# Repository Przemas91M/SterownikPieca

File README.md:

# Sterownik pompy pieca CO
Prosty sterownik pompy obiegowej pieca CO w oparciu o mikrokontroler ATmega328P-AU.  
Sterownik składa się z:
- czujnika temperatury DS18B20,
- wyświetlacza LCD 2x18,
- enkodera obrotowego dla zadawania nastaw temperatury,
- 2x przekaźniki do załączania pompy i buzzera ostrzegawczego.    
Sterownik załącza pompę, gdy temperatura wody w piecu osiągnie 30 st C.  
Powyżej 70 st C załącza się buzzer ostrzegawczy, aby nie zagotować wody w obiegu grzewczym.  
Gdy temperatura spadnie poniżej 30 st C, pompa jest wyłączana.

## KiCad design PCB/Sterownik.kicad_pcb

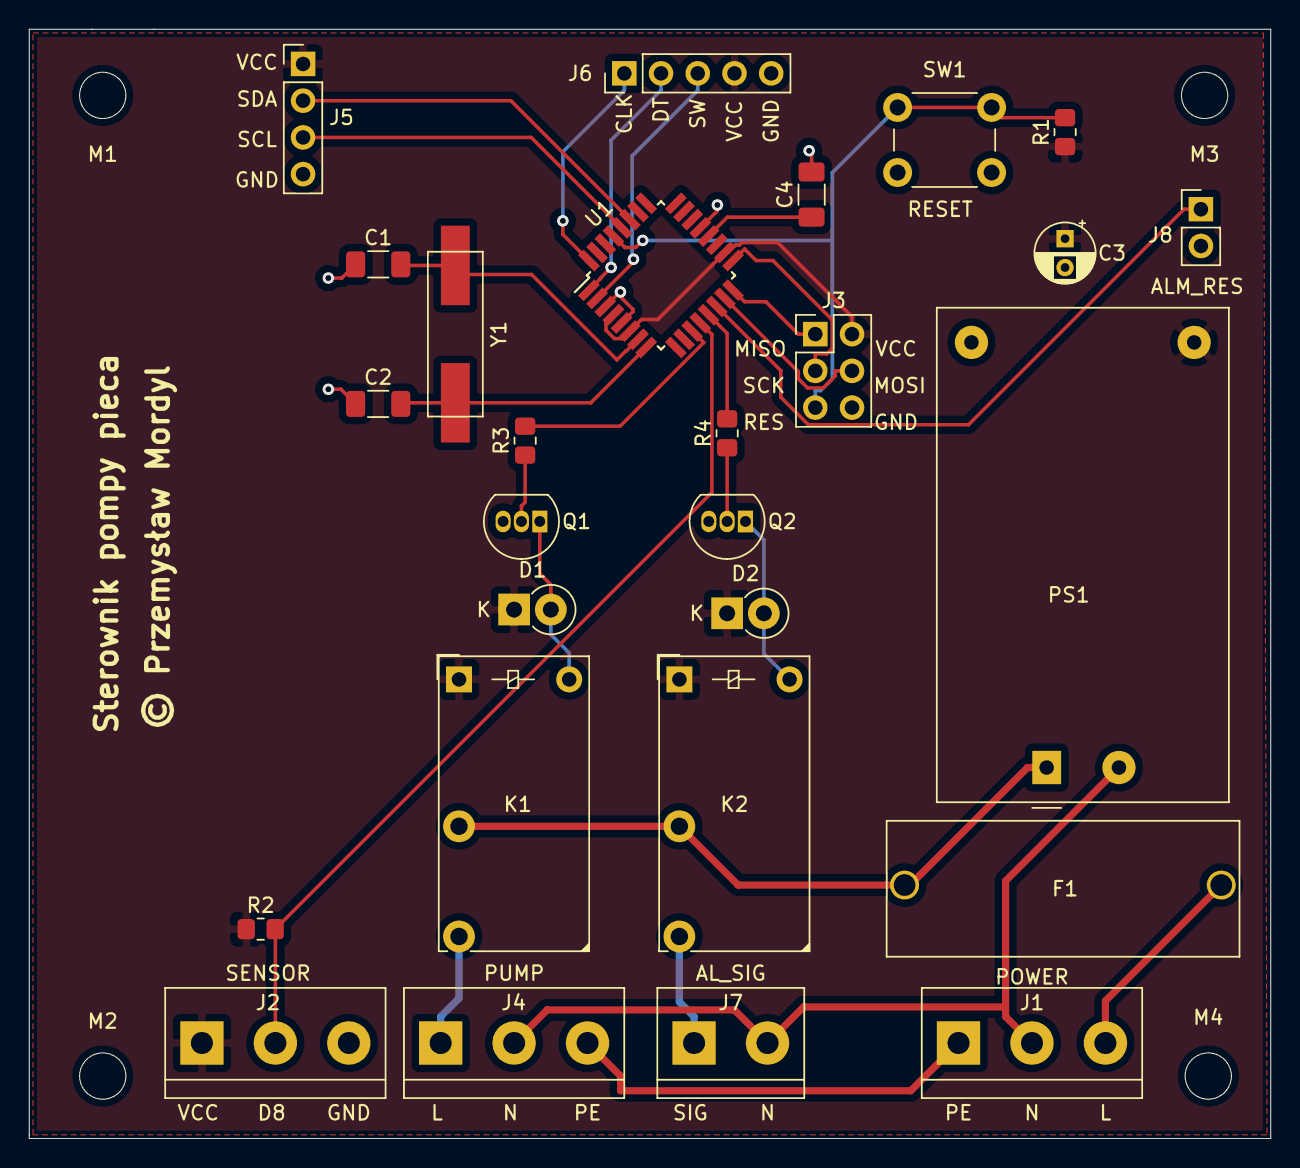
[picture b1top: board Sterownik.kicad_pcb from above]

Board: 2 copper layers, 85.9 x 76.7 mm, 31 parts (0 on the bottom side), 28 nets.

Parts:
C1, C2: C; C_1206_3216Metric_Pad1.33x1.80mm_HandSolder
C3: 220uF; CP_Radial_D4.0mm_P2.00mm
C4: 100nF; C_1206_3216Metric_Pad1.33x1.80mm_HandSolder
D1, D2: 1N4007; D_DO-41_SOD81_P2.54mm_Vertical_KathodeUp
F1: 1A; FuseHolder PTF-78
J1: Zasilanie 230VAC; TerminalBlock_bornier-3_P5.08mm
J2: Złącze DS18B20; TerminalBlock_bornier-3_P5.08mm
J3: Conn_02x03_Odd_Even; PinHeader_2x03_P2.54mm_Vertical
J4: Złącze pompy; TerminalBlock_bornier-3_P5.08mm
J5: Wyświetlacz LCD; PinHeader_1x04_P2.54mm_Vertical
J6: Enkoder obrotowy; PinHeader_1x05_P2.54mm_Vertical
J7: Złącze brzęczyka; TerminalBlock_bornier-2_P5.08mm
J8: Złącze kasowania alarmu; PinHeader_1x02_P2.54mm_Vertical
K1: Załączenie pompy; Relay_SPST_Finder_32.21-x300
K2: Załączenie sygnalizatora alarmu; Relay_SPST_Finder_32.21-x300
M1, M2, M3, M4: MountingHole_3.2mm_M3_DIN965
PS1: HLK-PM01; Converter_ACDC_HiLink_HLK-PMxx
Q1, Q2: BC182; TO-92_Inline
R1: 10K; R_0805_2012Metric_Pad1.20x1.40mm_HandSolder
R2, R3, R4: 4,7K; R_0805_2012Metric_Pad1.20x1.40mm_HandSolder
SW1: SW_Push; SW_PUSH_6mm
U1: ATmega328P-AU; TQFP-32_7x7mm_P0.8mm
Y1: Crystal; Crystal_16MHz_SMD

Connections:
/L: F1.2, J1.3
/N: J1.2, J4.2, J7.2, PS1.2
/PE: J1.1, J4.3
A4: J5.2, U1.27
A5: J5.3, U1.28
D2: J6.1, U1.32
D3: J6.2, U1.1
D4: J6.3, U1.2
D7: R3.2, U1.11
D8: J2.2, R2.2, U1.12
D9: R4.2, U1.13
D10: J8.1, U1.14
D11\MOSI: J3.4, U1.15
D12\MISO: J3.1, U1.16
D13\SCK: J3.3, U1.17
GND: C1.1, C2.1, C3.2, C4.2, J2.3, J3.6, J5.4, J6.5, J8.2, PS1.3, Q1.3, Q2.3, SW1.1, U1.3, U1.5, U1.21
unnamed: C1.2, U1.7, Y1.1
unnamed: C2.2, U1.8, Y1.2
unnamed: C4.1, U1.20
unnamed: D1.2, K1.A2, Q1.1
unnamed: D2.2, K2.A2, Q2.1
unnamed: F1.1, K1.11, K2.11, PS1.1
unnamed: J4.1, K1.14
unnamed: J7.1, K2.14
unnamed: Q1.2, R3.1
unnamed: Q2.2, R4.1
RESET: J3.5, R1.2, SW1.2, U1.29
VCC: C3.1, D1.1, D2.1, J2.1, J3.2, J5.1, J6.4, K1.A1, K2.A1, PS1.4, R1.1, R2.1, U1.4, U1.6, U1.18

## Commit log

2021-03-23 Add files via upload
    Initial commit

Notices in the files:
PCB/Sterownik.kicad_pcb:
© Przemysław Mordyl
